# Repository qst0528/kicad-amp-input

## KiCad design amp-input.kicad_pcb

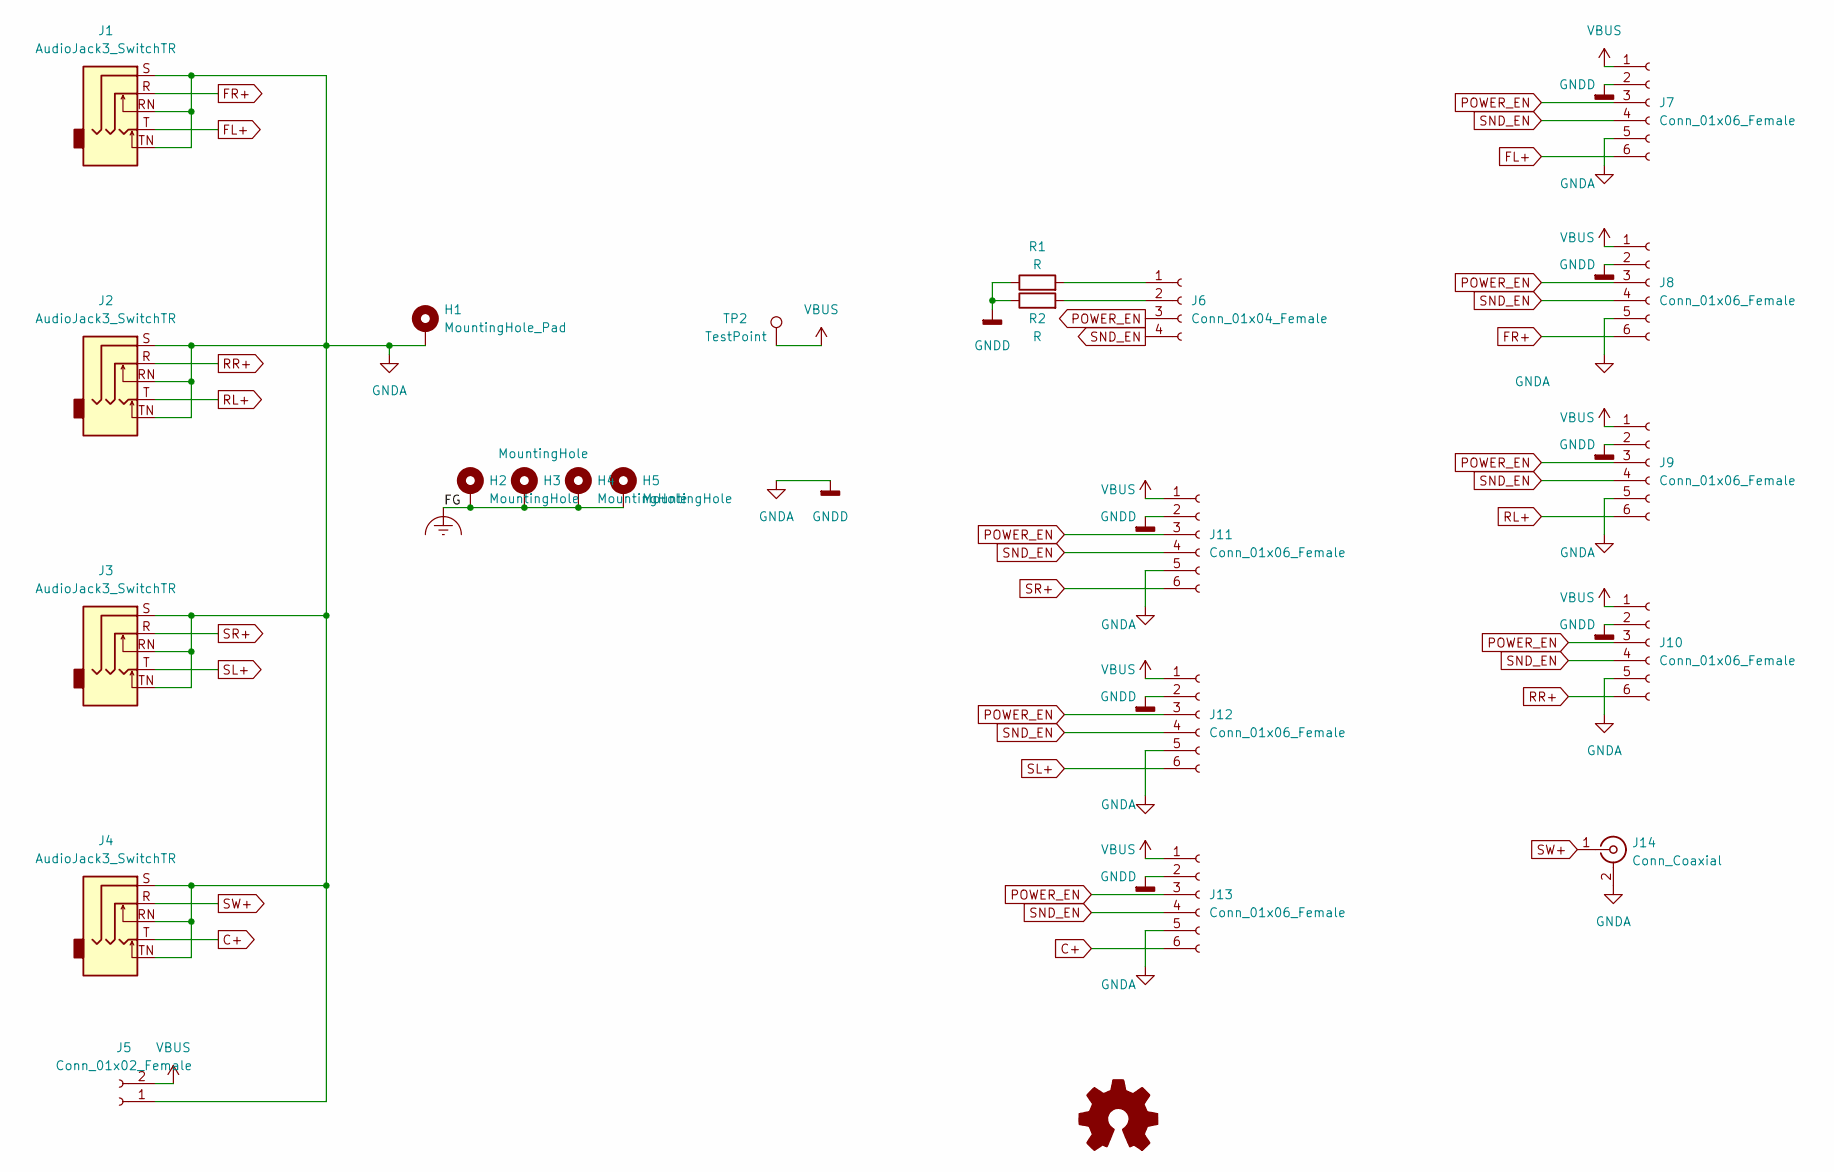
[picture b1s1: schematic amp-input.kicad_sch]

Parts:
H1: MountingHole_Pad; MountingHole_5.3mm_M5_Pad_Via
H2, H3, H4, H5: MountingHole; MountingHole_3.2mm_M3_DIN965_Pad_TopBottom
J1, J2, J3, J4: AudioJack3_SwitchTR; Jack_3.5mm_CUI_SJ1-3525N_Horizontal
J5: Conn_01x02_Female; JST_VH_B2P-VH_1x02_P3.96mm_Vertical
J6: Conn_01x04_Female; JST_XH_B4B-XH-A_1x04_P2.50mm_Vertical
J7, J8, J9, J10, J11, J12, J13: Conn_01x06_Female; JST_VH_B6P-VH_1x06_P3.96mm_Vertical
J14: Conn_Coaxial; RJ-2410N
LOGO1: Logo_Open_Hardware_Small; KiCad-Logo2_12mm_SilkScreen
R1, R2: R; R_0603_1608Metric_Pad0.98x0.95mm_HandSolder
TP2: TestPoint; TestPoint_Pad_D2.0mm

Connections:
C+: J4.T, J13.6
Earth_Clean: H2.1, H3.1, H4.1, H5.1
FL+: J1.T, J7.6
FR+: J1.R, J8.6
GNDA: H1.1, J1.RN, J1.S, J1.TN, J2.RN, J2.S, J2.TN, J3.RN, J3.S, J3.TN, J4.RN, J4.S, J4.TN, J5.1, J7.2, J7.5, J8.2, J8.5, J9.2, J9.5, J10.2, J10.5, J11.2, J11.5, J12.2, J12.5, J13.2, J13.5, J14.2 (Ext), R1.1, R2.1
unnamed: J6.1, R1.2
unnamed: J6.2, R2.2
POWER_EN: J6.3, J7.3, J8.3, J9.3, J10.3, J11.3, J12.3, J13.3
RL+: J2.T, J9.6
RR+: J2.R, J10.6
SL+: J3.T, J12.6
SND_EN: J6.4, J7.4, J8.4, J9.4, J10.4, J11.4, J12.4, J13.4
SR+: J3.R, J11.6
SW+: J4.R, J14.1 (In)
VBUS: J5.2, J7.1, J8.1, J9.1, J10.1, J11.1, J12.1, J13.1, TP2.1

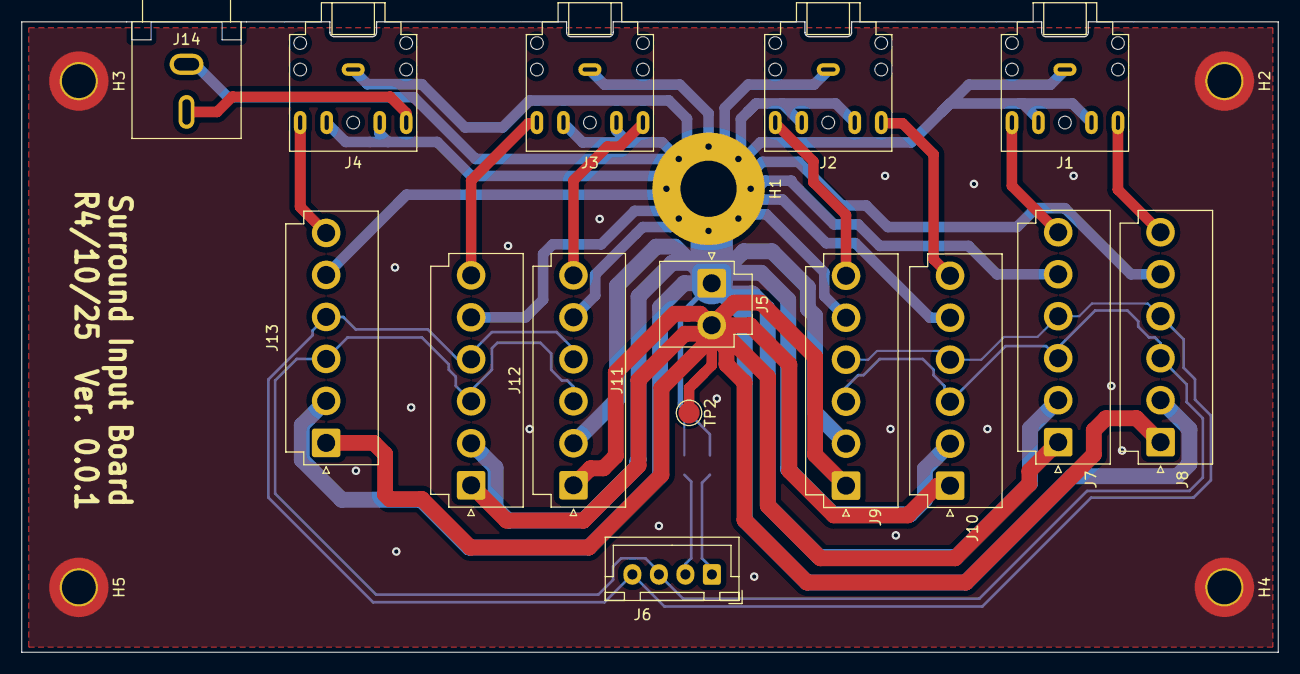
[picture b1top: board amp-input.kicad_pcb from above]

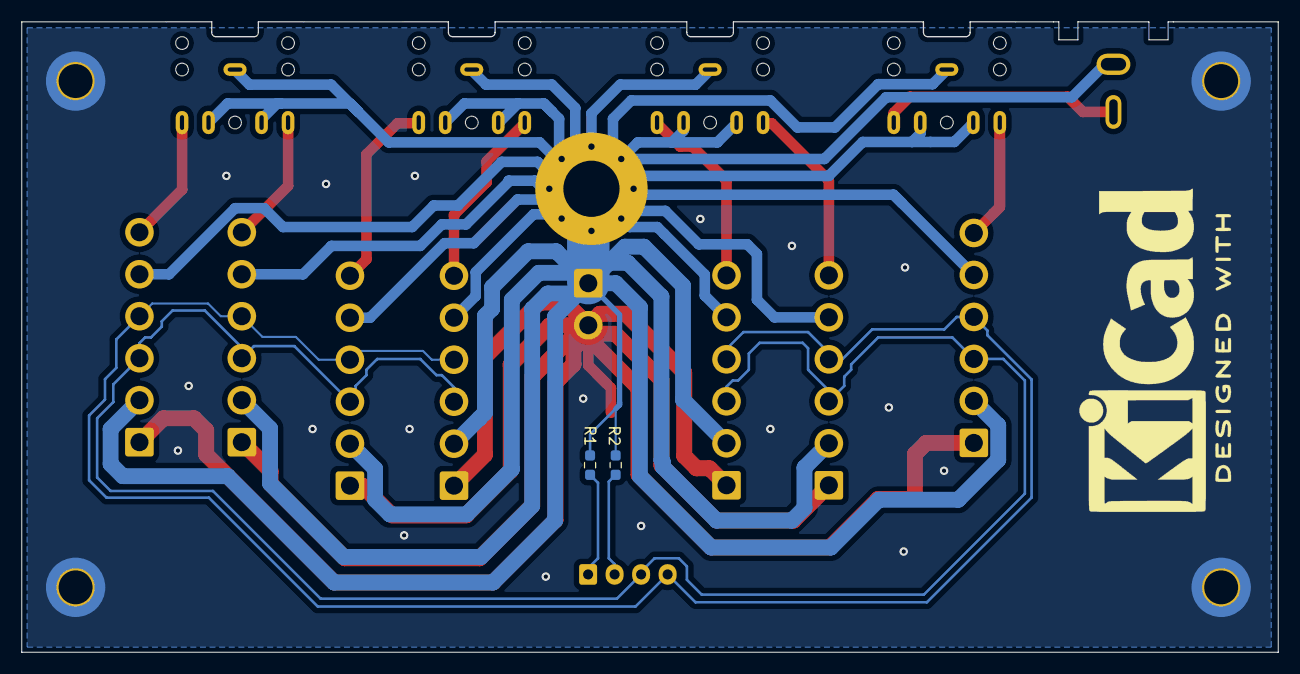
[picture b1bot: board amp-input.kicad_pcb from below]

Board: 2 copper layers, 118.5 x 59.5 mm, 23 parts (3 on the bottom side), 15 nets.

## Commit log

2023-02-20 Initialize repo with prototype
